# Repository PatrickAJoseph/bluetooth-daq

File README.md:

# bluetooth-daq
A simple low-speed Bluetooth enabled DAQ consisting of HV/LV voltage, current measurement, LV analog I/O, resistance measurement, UART, I2C & SPI communication interfaces and a high speed ADC combining multiple functionalities within one device. The device can be operated through a mobile/PC application via Bluetooth or through RS-485 interface. 16 devices can be connected to the RS-485 interface.

## Goal of the product
1. Reduce the number of induvidual electronic test equipment required for electronic hardware/software development.

2. Combine commonly used electronic test functions within a single device

3. Enable versatile interface to the device (RS485, Bluetooth, Web) and test automation support to reduce effort of manual testing.

## Features of the product

### Hardware features

1. 16 low-speed logic level digital inputs (+/ 3.3V) (maximum sampling rate of 100 SPS)
2. 16 low-speed logic level digital outputs (0-3V) with maximum current limit of 5mA / channel (maximum sampling rate of 100 SPS).
3. 2 channel bi-polar differential high-resolution analog inputs (+/-, 50V, 6 digits) with maximum sampling rate of 2 kSPS/channel in single channel sampling mode.
4. 2 channel high speed bipolar differential analog acquisition channels (maximum input signal frequency of 10kHz)
5. 1 UART communication instance (UART_TX, UART_RX) with maximum baud rate of 115200.
6. 1 I2C communication instance (I2C_SDA, I2C_SCL) with maximum clock speed of 400 kHz.
7. 1 SPI communication instance (SPI_MOSI, SPI_MISO, SPI_nCS, SPI_SCLK) with maximum clock speed of 4 MHz.
8. 8 channel differental bi-polar low voltage analog inputs +/- 15V range.
9. 2 current measurement inputs (+/- 50V common mode voltage, and maximum current of 3A).
10. 2 resistance measurement inputs ( 1 ohm to 1 MOhm ).
11. 2 thermistor temperature measurement channels.
12. 8 low speed DC analog outputs.
13. RS-485 interface for remote control.

### Software features

1. RS-485 control of device through PC.
2. Bluetooth control of device from PC/Mobile application.
3. Firmware upgrade through Bluetooth using TI Simplelink Connect app.
4. Simple Web GUI interface for control of device.
5. Python scripting support for remote control of device from PC.
6. LabVIEW support for the device.

## Hardware block diagram

.png>)

### High voltage analog inputs

The device provides 2 high voltage analog inputs with a range of +/- 50V and maximum input frequency of 200 Hz. The high voltage analog input front end attenuates the input voltage signal and adds bias to meet voltage level requirements of the sigma-delta ADC inputs.

### Current inputs

The device provides 2 current inputs with common mode voltage upto +/- 50V and a range of +/- 3A. The voltage drop across the
current measurement terminal is 0.1V/A.

### Low voltage analog inputs

The device provides 8 channel +/- 15V low voltage analog inputs.
Maximum input frequency per channel is set to 200 Hz.

### Resistance measurement

The device provides 2 channel resistance measurement feature.
The supported resistance measurement range is 1 ohm to 1 MOhm.

### High speed acquisition channels

The device provides 2 single ended high speed analog signal
acquisition channels with sampling frequency of 200 kSPS per
channel, limiting the combined input signal frequency to 10kHz.

### Thermistor temperature measurement channels

The device provides 2 thermistor temperature measurement channels.
The reference voltage for the thermistor interface is 3.3V and reference resistance is 10k. The device comes with a calibration table for a 10K NTC. If user uses any other NTC, then, the calibration table for thermistor has to be manually entered by the user via software.

### Sigma-Delta ADC

The heart of most of the analog to digital conversions is carried out by a 24-bit sigma-delta ADC (ADS131M02: https://www.ti.com/lit/ds/symlink/ads131m02.pdf?ts=1769953054375&ref_url=https%253A%252F%252Fwww.ti.com%252Fproduct%252FADS131M02).

The input to each channel of the ADC is multiplexed with the help of analog multiplexer (CD4051: https://www.ti.com/lit/ds/symlink/cd4051b.pdf)

### Low speed analog outputs

The device provides 8 analog outputs with range +/- 10V. Since a sample and hold circuit is used at the output stage, the output current limit is 1mA and so an external buffer must be used. The DAC used in the solution is DAC101C081 (https://www.ti.com/product/DAC101C081)

### SPI SRAM

The device uses a 1 MBit SRAM to store samples acquired from various modules such as high speed ADC, digital inputs, digital output patterns etc. The SRAM used is 23LCV1024 (https://ww1.microchip.com/downloads/en/DeviceDoc/25156A.pdf)

### Digital inputs and outputs

The device provides 16 digital inputs and digital outputs. The digital inputs are read by the MCU through a 74HC165 shift register (https://www.ti.com/lit/ds/symlink/sn74hc165.pdf) and the digital outputs are transferred through 74HC595 shift register (https://www.ti.com/lit/ds/symlink/sn74hc595.pdf).

The digital inputs have a range of +/- 3.3V in order to provided reverse voltage protection. The digital outputs have a current limit of 5mA per channel. 

### Indicator LEDs

There are three indicator LEDs, 1 green, 1 red and 1 yellow.
The green LED indicates status of any ongoing communication between host and the device. The red LED indicates any error which has occured in the device. The yello LED indicates that a firmware upgrade is going on the device.

### MCU

The microcontroller used in the device is CC2340R52 (https://www.ti.com/product/CC2340R5/part-details/CC2340R52E0RGER) which is an ARM Cortex-M0+ MCU with 512 KB FLASH and 36 KB RAM.

### UART, I2C and SPI interfaces

The device provides an SPI, I2C and a UART interface which can be used by the user to transfer bytes to external devices under test.

## Software block diagram

### RTOS

The software uses FreeRTOS operating system. This is required by the TI Bluetooth Stack and also for multithreading purposes.

### Soc Peripheral Drivers

The following SoC peripheral drivers are required by the product.

|       Driver          |           Description                            |
|-----------------------|--------------------------------------------------|
|       ADC             |  Required by the high speed analog input module  |
|       SPI             |  Required for accessing the shift registers <br> and the external SRAM memory |
|       I2C             |  Required to control DAC IC on the board         |
|       UART            |  Required for interaction with host PC through RS-485 interface         |
|       GPIO            |   Required by all other drivers                  |

### Board Peripheral Drivers

|       Driver          |                       Purpose                             |
|-----------------------|-----------------------------------------------------------|
|    ADS131M02          |    Controls the 24-bit Sigma-Delta ADC. Performs common operations such as setting ADC PGA gain, calibration, sample acquisition etc. |
|    SN75HC595          |  Write data to the digital outputs through shift registers |
|   SN75HC165           |  Read data from the SOPI shift registers |
|   DAC101C081          |  Required for controlling the external 10-bit for setting the desired output voltage. Also, supports calibration. |
|   23LCV1024           |   Controls the external SRAM IC. Provides read and write APIs for the external memory |

### Bootloader and Firmware upgrade

The device supports over the air firmware upgrade through the TI Simplelink Connect application for Mobile (https://www.bing.com/search?q=TI+Simplelink+connect&cvid=ed73fef019854968bf1f31853ef2398b&gs_lcrp=EgRlZGdlKgYIABBFGDkyBggAEEUYOTIGCAEQABhAMgYIAhAAGEAyBggDEAAYQDIGCAQQABhAMgYIBRAAGEAyBggGEAAYQNIBCDMyNjZqMGo5qAIIsAIB&FORM=ANAB01&PC=U531). Firmware upgrade over Bluetooth is only supported for mobile phones and not for laptop.

### Bluetooth stack

The device uses the Texas Instruments Bluetooth stack. This stack is required for Bluetooth over the air firmware upgrade and also serves as an interface between the mobile/PC and the device.

### SSCP stack (serial) & SSCP stack (bluetooth)

The SSCP (Simple System Control Protocol) is the transport protocol which is used by the device to interact with the host via serial interface or Bluetooth. Each interface requires a seperate SSCP responder stack instance. For more details about the SSCP protocol refer to the following Git repository: https://github.com/PatrickAJoseph/simple-system-control-protocol.

### SSCP application interface

This software component defines the register callback functions, register definitions related to the application for the SSCP stack.

### SSCP responder stack processing task (serial & Bluetooth)

This software components receives bytes from the interface (serial/Bluetooth) and sends the received byets to the SSCP stack for processing.

### Device configuration manager

Validates the configuration provided by the user. Also, stores and loads device settings in non-volatile storage.

### High speed ADC data acquisition handler

Acquires samples from the high speed acquisition ADC channels and stores conversion results in the external SRAM. Users can then read back the samples stored in the SRAM.

### Digital I/O handler

Used to control the digital inputs and the digital outputs of the device through the shift registers as described in the hardware section. Supports setting, clearing, toggling each DO pin and reading state of DI pins.

### Analog I/O handler

Controls calibration of each high voltage analog input channel, current channel, resistance measurement channel, thermistor temperature measurement channel and analog output channel. Acquires samples from the analog input channels, performs filtering and then adds calibration parameters to provide processed results. Manages the multiplexing of different analog inputs to the input channels of the sigma-delta converter through the multiplexer.

### External SRAM handler

The external SRAM handler is an abstraction component for the external SRAM driver. Responsible for reading and writing data application defined memory regions in the external SRAM memory via the SPI interface.

### Digital interfaces handler (UART, SPI, I2C)

Used to handle received communication interface commands (such as transmit, receive commands) for UART, I2C and SPI protocols. Can handle multiple byte transfer for all interfaces and stores received bytes in the external SRAM for post processing.

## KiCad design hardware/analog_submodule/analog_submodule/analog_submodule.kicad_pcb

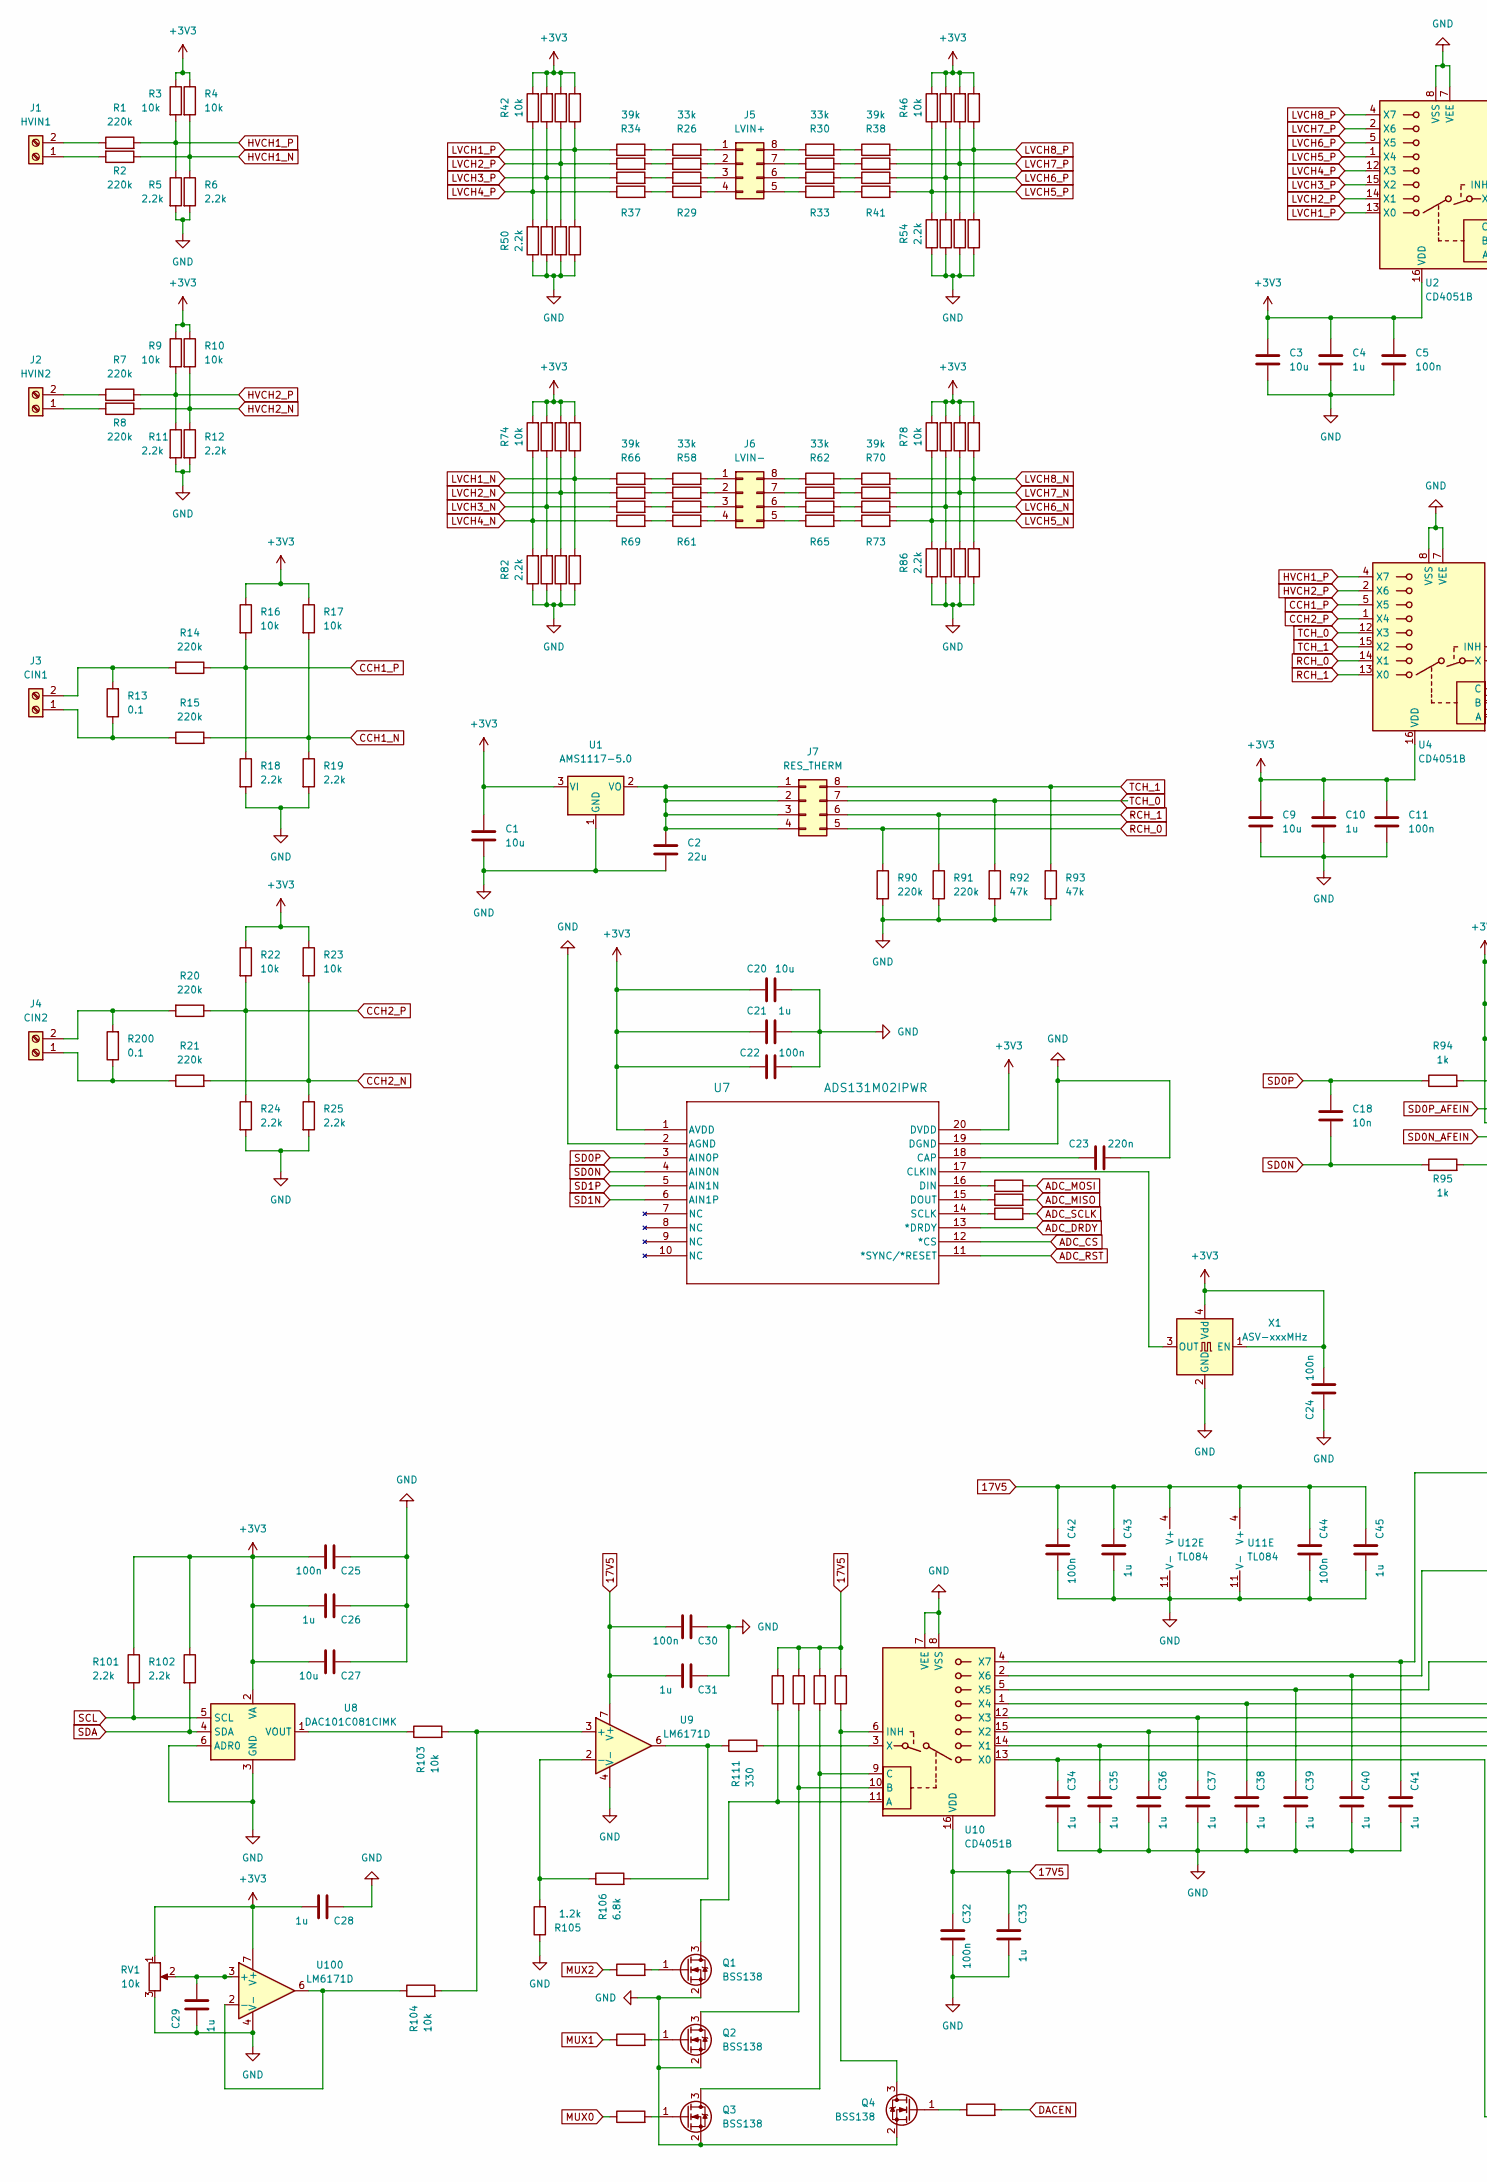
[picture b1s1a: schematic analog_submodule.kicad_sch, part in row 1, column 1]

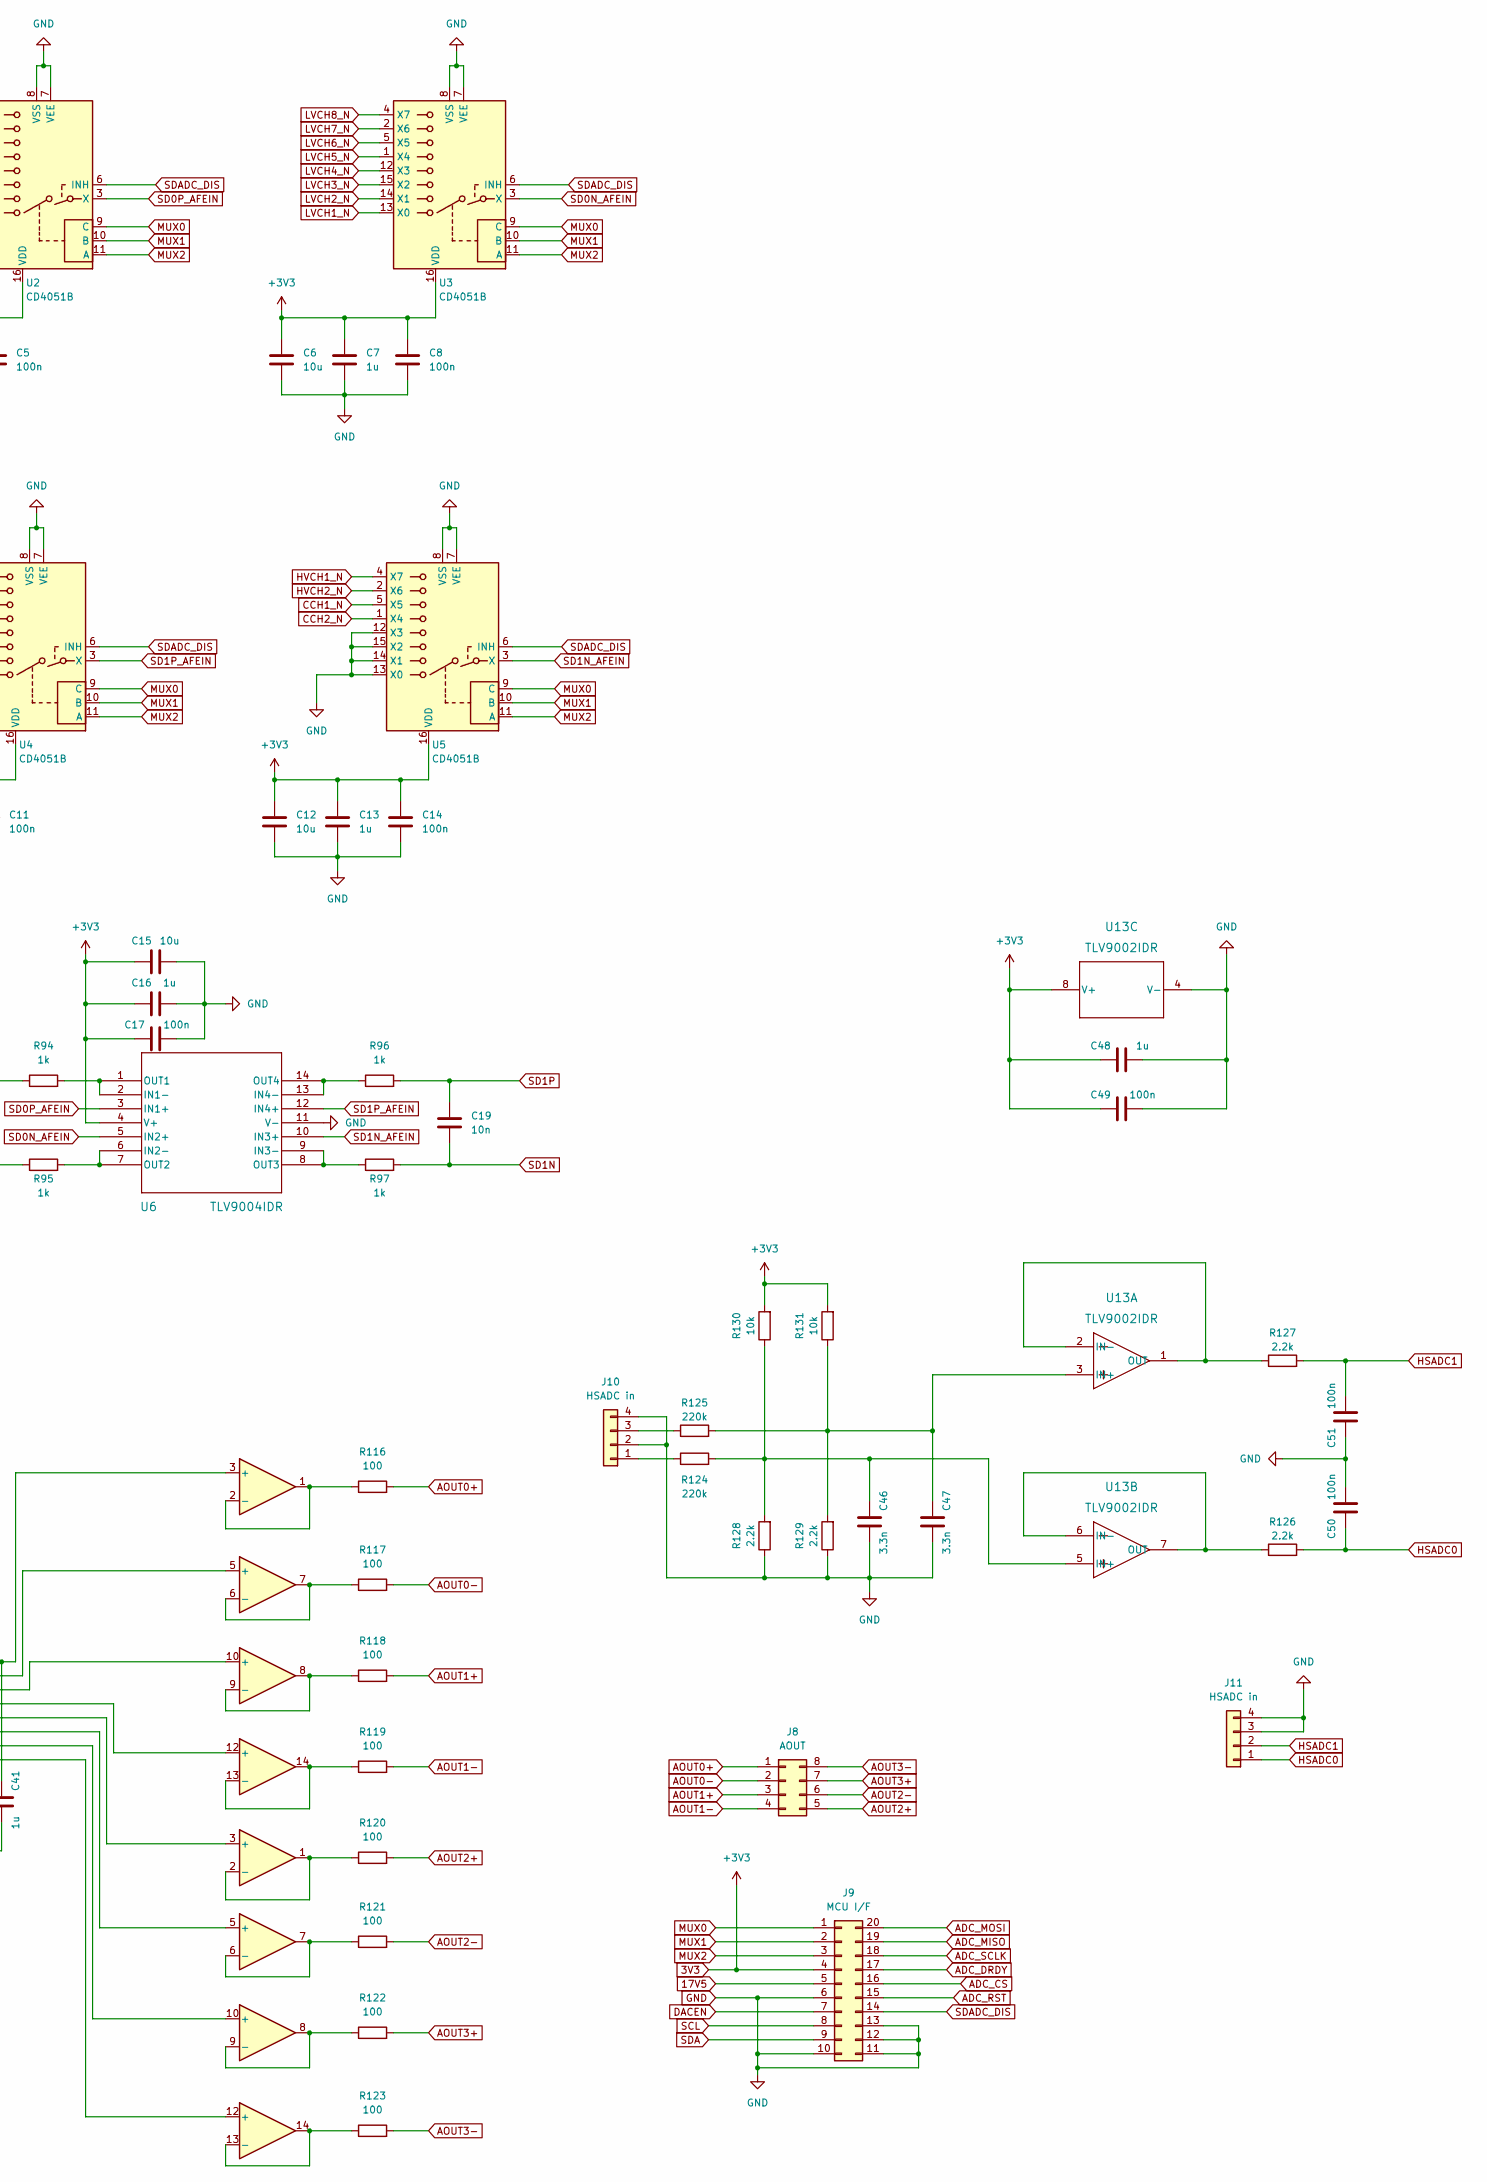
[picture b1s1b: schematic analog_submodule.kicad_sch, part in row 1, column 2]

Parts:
C1, C3, C6, C9, C12, C15, C20, C27: 10u; C_0805_2012Metric_Pad1.18x1.45mm_HandSolder
C2: 22u; C_0805_2012Metric_Pad1.18x1.45mm_HandSolder
C4, C7, C10, C13, C16, C21, C26, C28, C29, C31, C33, C34, C35, C36, C37, C38, C39, C40, C41, C43, C45, C48: 1u; C_0805_2012Metric_Pad1.18x1.45mm_HandSolder
C5, C8, C11, C14, C17, C22, C24, C25, C30, C32, C42, C44, C49, C50, C51: 100n; C_0805_2012Metric_Pad1.18x1.45mm_HandSolder
C18, C19: 10n; C_0805_2012Metric_Pad1.18x1.45mm_HandSolder
C23: 220n; C_0805_2012Metric_Pad1.18x1.45mm_HandSolder
C46, C47: 3.3n; C_0805_2012Metric_Pad1.18x1.45mm_HandSolder
J1: HVIN1; PhoenixContact_MCV_1,5_2-G-5.08_1x02_P5.08mm_Vertical
J2: HVIN2; PhoenixContact_MCV_1,5_2-G-5.08_1x02_P5.08mm_Vertical
J3: CIN1; PhoenixContact_MCV_1,5_2-G-5.08_1x02_P5.08mm_Vertical
J4: CIN2; PhoenixContact_MCV_1,5_2-G-5.08_1x02_P5.08mm_Vertical
J5: LVIN+; PinHeader_2x04_P2.54mm_Vertical
J6: LVIN-; PinHeader_2x04_P2.54mm_Vertical
J7: RES_THERM; PinHeader_2x04_P2.54mm_Vertical
J8: AOUT; PinHeader_2x04_P2.54mm_Vertical
J9: MCU I/F; PinHeader_2x10_P2.54mm_Vertical
J10, J11: HSADC in; PinHeader_1x04_P2.54mm_Vertical
Q1, Q2, Q3, Q4: BSS138; SOT-23
R1, R2, R7, R8, R14, R15, R20, R21, R90, R91, R124, R125: 220k; R_0805_2012Metric_Pad1.20x1.40mm_HandSolder
R3, R4, R9, R10, R16, R17, R22, R23, R42, R43, R44, R45, R46, R47, R48, R49, R74, R75, R76, R77, R78, R79, R80, R81, R103, R104, R107, R108, R109, R110, R130, R131: 10k; R_0805_2012Metric_Pad1.20x1.40mm_HandSolder
R5, R6, R11, R12, R18, R19, R24, R25, R50, R51, R52, R53, R54, R55, R56, R57, R82, R83, R84, R85, R86, R87, R88, R89, R101, R102, R126, R127, R128, R129: 2.2k; R_0805_2012Metric_Pad1.20x1.40mm_HandSolder
R13, R200: 0.1; R_2512_6332Metric_Pad1.40x3.35mm_HandSolder
R26, R27, R28, R29, R30, R31, R32, R33, R58, R59, R60, R61, R62, R63, R64, R65: 33k; R_0805_2012Metric_Pad1.20x1.40mm_HandSolder
R34, R35, R36, R37, R38, R39, R40, R41, R66, R67, R68, R69, R70, R71, R72, R73: 39k; R_0805_2012Metric_Pad1.20x1.40mm_HandSolder
R92, R93: 47k; R_0805_2012Metric_Pad1.20x1.40mm_HandSolder
R94, R95, R96, R97, R112, R113, R114, R115: 1k; R_0805_2012Metric_Pad1.20x1.40mm_HandSolder
R98, R99, R100: 22; R_0805_2012Metric_Pad1.20x1.40mm_HandSolder
R105: 1.2k; R_0805_2012Metric_Pad1.20x1.40mm_HandSolder
R106: 6.8k; R_0805_2012Metric_Pad1.20x1.40mm_HandSolder
R111: 330; R_0805_2012Metric_Pad1.20x1.40mm_HandSolder
R116, R117, R118, R119, R120, R121, R122, R123: 100; R_0805_2012Metric_Pad1.20x1.40mm_HandSolder
RV1: 10k; Potentiometer_Bourns_3266Y_Vertical
U1: AMS1117-5.0; SOT-223-3_TabPin2
U2, U3, U4, U5, U10: CD4051B; D16
U6: TLV9004IDR; SOIC-14_3.9x8.7mm_P1.27mm
U7: ADS131M02IPWR; TSSOP-20_4.4x6.5mm_P0.65mm
U8: DAC101C081CIMK; SOT-23-6
U9, U100: LM6171D; SOIC-8_3.9x4.9mm_P1.27mm
U11, U12: TL084; SOIC-14_3.9x8.7mm_P1.27mm
U13: TLV9002IDR; SOIC-8_3.9x4.9mm_P1.27mm
X1: ASV-xxxMHz; Oscillator_SMD_Abracon_ASV-4Pin_7.0x5.1mm

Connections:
3V3: C1.1, C3.1, C4.1, C5.1, C6.1, C7.1, C8.1, C9.1, C10.1, C11.1, C12.1, C13.1, C14.1, C15.1, C16.1, C17.1, C20.1, C21.1, C22.1, C24.2, C25.2, C26.2, C27.2, C28.2, C48.1, C49.1, J9.4, R3.1, R4.1, R9.1, R10.1, R16.1, R17.1, R22.1, R23.1, R42.2, R43.2, R44.2, R45.2, R46.2, R47.2, R48.2, R49.2, R74.2, R75.2, R76.2, R77.2, R78.2, R79.2, R80.2, R81.2, R101.1, R102.1, R130.2, R131.2, RV1.1, U1.3 (VI), U2.16 (VDD), U3.16 (VDD), U4.16 (VDD), U5.16 (VDD), U6.4 (V+), U7.1 (AVDD), U7.20 (DVDD), U8.2 (VA), U13.8 (V+), U100.7 (V+), X1.1 (EN), X1.4 (Vdd)
17V5: C30.2, C31.2, C32.1, C33.1, C42.1, C43.1, C44.1, C45.1, J9.5, R107.2, R108.2, R109.2, R110.2, U9.7 (V+), U10.16 (VDD), U11.4 (V+), U12.4 (V+)
ADC_CS: J9.16, U7.12 (*CS)
ADC_DRDY: J9.17, U7.13 (*DRDY)
ADC_MISO: J9.19, R99.2
ADC_MOSI: J9.20, R98.2
ADC_RST: J9.15, U7.11 (*SYNC/*RESET)
ADC_SCLK: J9.18, R100.2
AOUT0+: J8.1, R116.2
AOUT0-: J8.2, R117.2
AOUT1+: J8.3, R118.2
AOUT1-: J8.4, R119.2
AOUT2+: J8.5, R120.2
AOUT2-: J8.6, R121.2
AOUT3+: J8.7, R122.2
AOUT3-: J8.8, R123.2
CCH1_N: R15.2, R17.2, R19.1, U5.5 (X5)
CCH1_P: R14.1, R16.2, R18.1, U4.5 (X5)
CCH2_N: R21.2, R23.2, R25.1, U5.1 (X4)
CCH2_P: R20.1, R22.2, R24.1, U4.1 (X4)
DACEN: J9.7, R115.2
GND: C1.2, C2.2, C3.2, C4.2, C5.2, C6.2, C7.2, C8.2, C9.2, C10.2, C11.2, C12.2, C13.2, C14.2, C15.2, C16.2, C17.2, C20.2, C21.2, C22.2, C23.2, C24.1, C25.1, C26.1, C27.1, C28.1, C29.2, C30.1, C31.1, C32.2, C33.2, C34.2, C35.2, C36.2, C37.2, C38.2, C39.2, C40.2, C41.2, C42.2, C43.2, C44.2, C45.2, C46.2, C47.2, C48.2, C49.2, C50.2, C51.1, J9.6, J9.10, J9.11, J9.12, J9.13, J10.2, J10.4, J11.3, J11.4, Q1.2 (S), Q2.2 (S), Q3.2 (S), Q4.2 (S), R5.2, R6.2, R11.2, R12.2, R18.2, R19.2, R24.2, R25.2, R50.1, R51.1, R52.1, R53.1, R54.1, R55.1, R56.1, R57.1, R82.1, R83.1, R84.1, R85.1, R86.1, R87.1, R88.1, R89.1, R90.2, R91.2, R92.2, R93.2, R105.1, R128.1, R129.1, RV1.3, U1.1 (GND), U2.7 (VEE), U2.8 (VSS), U3.7 (VEE), U3.8 (VSS), U4.7 (VEE), U4.8 (VSS), U5.7 (VEE), U5.8 (VSS), U5.12 (X3), U5.13 (X0), U5.14 (X1), U5.15 (X2), U6.11 (V-), U7.2 (AGND), U7.19 (DGND), U8.3 (GND), U8.6 (ADR0), U9.4 (V-), U10.7 (VEE), U10.8 (VSS), U11.11 (V-), U12.11 (V-), U13.4 (V-), U100.4 (V-), X1.2 (GND)
HSADC0: C50.1, J11.1, R126.2
HSADC1: C51.2, J11.2, R127.2
HVCH1_N: R2.1, R4.2, R6.1, U5.4 (X7)
HVCH1_P: R1.2, R3.2, R5.1, U4.4 (X7)
HVCH2_N: R8.1, R10.2, R12.1, U5.2 (X6)
HVCH2_P: R7.2, R9.2, R11.1, U4.2 (X6)
LVCH1_N: R66.1, R77.1, R85.2, U3.13 (X0)
LVCH1_P: R34.1, R45.1, R53.2, U2.13 (X0)
LVCH2_N: R67.1, R76.1, R84.2, U3.14 (X1)
LVCH2_P: R35.1, R44.1, R52.2, U2.14 (X1)
LVCH3_N: R68.1, R75.1, R83.2, U3.15 (X2)
LVCH3_P: R36.1, R43.1, R51.2, U2.15 (X2)
LVCH4_N: R69.1, R74.1, R82.2, U3.12 (X3)
LVCH4_P: R37.1, R42.1, R50.2, U2.12 (X3)
LVCH5_N: R73.2, R78.1, R86.2, U3.1 (X4)
LVCH5_P: R41.2, R46.1, R54.2, U2.1 (X4)
LVCH6_N: R72.2, R79.1, R87.2, U3.5 (X5)
LVCH6_P: R40.2, R47.1, R55.2, U2.5 (X5)
LVCH7_N: R71.2, R80.1, R88.2, U3.2 (X6)
LVCH7_P: R39.2, R48.1, R56.2, U2.2 (X6)
LVCH8_N: R70.2, R81.1, R89.2, U3.4 (X7)
LVCH8_P: R38.2, R49.1, R57.2, U2.4 (X7)
MUX0: J9.1, R114.1, U2.9 (C), U3.9 (C), U4.9 (C), U5.9 (C)
MUX1: J9.2, R113.1, U2.10 (B), U3.10 (B), U4.10 (B), U5.10 (B)
MUX2: J9.3, R112.1, U2.11 (A), U3.11 (A), U4.11 (A), U5.11 (A)
unnamed: C2.1, J7.1, J7.2, J7.3, J7.4, U1.2 (VO)
unnamed: C23.1, U7.18 (CAP)
unnamed: C29.1, RV1.2, U100.3 (+)
unnamed: C34.1, U10.13 (X0), U12.12 (+)
unnamed: C35.1, U10.14 (X1), U12.10 (+)
unnamed: C36.1, U10.15 (X2), U12.5 (+)
unnamed: C37.1, U10.12 (X3), U12.3 (+)
unnamed: C38.1, U10.1 (X4), U11.12 (+)
unnamed: C39.1, U10.5 (X5), U11.10 (+)
unnamed: C40.1, U10.2 (X6), U11.5 (+)
unnamed: C41.1, U10.4 (X7), U11.3 (+)
unnamed: C46.1, R124.2, R128.2, R130.1, U13.5 (IN+)
unnamed: C47.1, R125.2, R129.2, R131.1, U13.3 (IN+)
unnamed: J1.1, R2.2
unnamed: J1.2, R1.1
unnamed: J2.1, R8.2
unnamed: J2.2, R7.1
unnamed: J3.1, R13.1, R15.1
unnamed: J3.2, R13.2, R14.2
unnamed: J4.1, R21.1, R200.1
unnamed: J4.2, R20.2, R200.2
unnamed: J5.1, R26.2
unnamed: J5.2, R27.2
unnamed: J5.3, R28.2
unnamed: J5.4, R29.2
unnamed: J5.5, R33.1
unnamed: J5.6, R32.1
unnamed: J5.7, R31.1
unnamed: J5.8, R30.1
unnamed: J6.1, R58.2
unnamed: J6.2, R59.2
unnamed: J6.3, R60.2
unnamed: J6.4, R61.2
unnamed: J6.5, R65.1
unnamed: J6.6, R64.1
unnamed: J6.7, R63.1
unnamed: J6.8, R62.1
unnamed: J10.1, R124.1
unnamed: J10.3, R125.1
unnamed: Q1.1 (G), R112.2
unnamed: Q1.3 (D), R107.1, U10.11 (A)
unnamed: Q2.1 (G), R113.2
unnamed: Q2.3 (D), R108.1, U10.10 (B)
unnamed: Q3.1 (G), R114.2
unnamed: Q3.3 (D), R109.1, U10.9 (C)
unnamed: Q4.1 (G), R115.1
unnamed: Q4.3 (D), R110.1, U10.6 (INH)
unnamed: R26.1, R34.2
unnamed: R27.1, R35.2
unnamed: R28.1, R36.2
unnamed: R29.1, R37.2
unnamed: R30.2, R38.1
unnamed: R31.2, R39.1
unnamed: R32.2, R40.1
unnamed: R33.2, R41.1
unnamed: R58.1, R66.2
unnamed: R59.1, R67.2
unnamed: R60.1, R68.2
unnamed: R61.1, R69.2
unnamed: R62.2, R70.1
unnamed: R63.2, R71.1
unnamed: R64.2, R72.1
unnamed: R65.2, R73.1
unnamed: R94.2, U6.1 (OUT1), U6.2 (IN1-)
unnamed: R95.2, U6.6 (IN2-), U6.7 (OUT2)
unnamed: R96.1, U6.13 (IN4-), U6.14 (OUT4)
unnamed: R97.1, U6.8 (OUT3), U6.9 (IN3-)
unnamed: R98.1, U7.16 (DIN)
unnamed: R99.1, U7.15 (DOUT)
unnamed: R100.1, U7.14 (SCLK)
unnamed: R103.1, U8.1 (VOUT)
unnamed: R103.2, R104.2, U9.3 (+)
unnamed: R104.1, U100.2 (-), U100.6
unnamed: R105.2, R106.1, U9.2 (-)
unnamed: R106.2, R111.1, U9.6
unnamed: R111.2, U10.3 (X)
unnamed: R116.1, U11.1, U11.2 (-)
unnamed: R117.1, U11.6 (-), U11.7
unnamed: R118.1, U11.8, U11.9 (-)
unnamed: R119.1, U11.13 (-), U11.14
unnamed: R120.1, U12.1, U12.2 (-)
unnamed: R121.1, U12.6 (-), U12.7
unnamed: R122.1, U12.8, U12.9 (-)
unnamed: R123.1, U12.13 (-), U12.14
unnamed: R126.1, U13.6 (IN-), U13.7 (OUT)
unnamed: R127.1, U13.1 (OUT), U13.2 (IN-)
unnamed: U7.17 (CLKIN), X1.3 (OUT)
RCH_0: J7.5, R90.1, U4.14 (X1)
RCH_1: J7.6, R91.1, U4.13 (X0)
SCL: J9.8, R101.2, U8.5 (SCL)
SD0N: C18.2, R95.1, U7.4 (AIN0N)
SD0N_AFEIN: U3.3 (X), U6.5 (IN2+)
SD0P: C18.1, R94.1, U7.3 (AIN0P)
SD0P_AFEIN: U2.3 (X), U6.3 (IN1+)
SD1N: C19.2, R97.2, U7.6 (AIN1P)
SD1N_AFEIN: U5.3 (X), U6.10 (IN3+)
SD1P: C19.1, R96.2, U7.5 (AIN1N)
SD1P_AFEIN: U4.3 (X), U6.12 (IN4+)
SDA: J9.9, R102.2, U8.4 (SDA)
SDADC_DIS: J9.14, U2.6 (INH), U3.6 (INH), U4.6 (INH), U5.6 (INH)
TCH_0: J7.7, R92.1, U4.12 (X3)
TCH_1: J7.8, R93.1, U4.15 (X2)

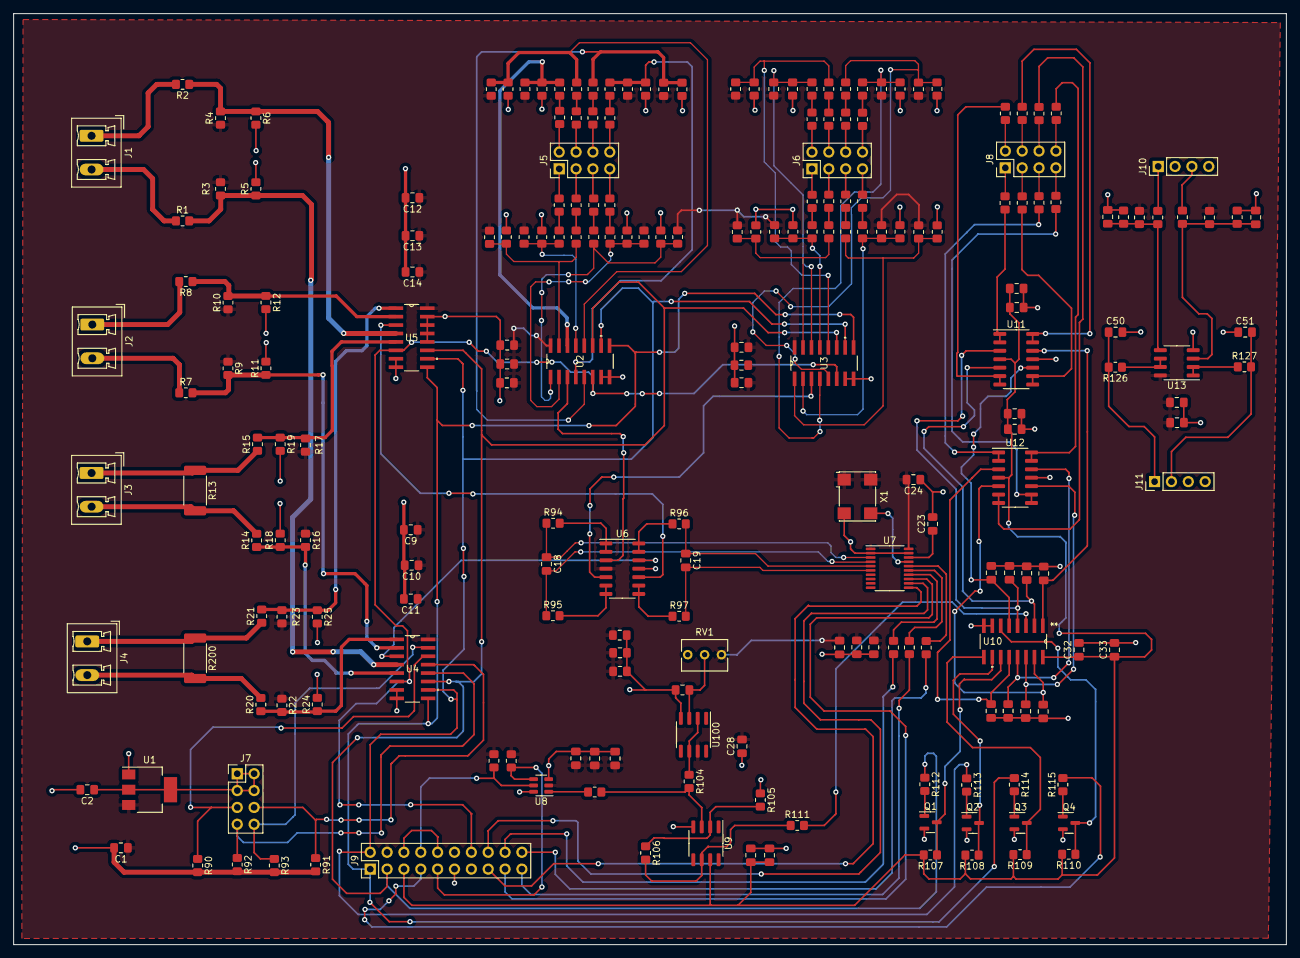
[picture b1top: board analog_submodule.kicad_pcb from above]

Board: 2 copper layers, 191.8 x 140.3 mm, 214 parts (0 on the bottom side), 149 nets.
